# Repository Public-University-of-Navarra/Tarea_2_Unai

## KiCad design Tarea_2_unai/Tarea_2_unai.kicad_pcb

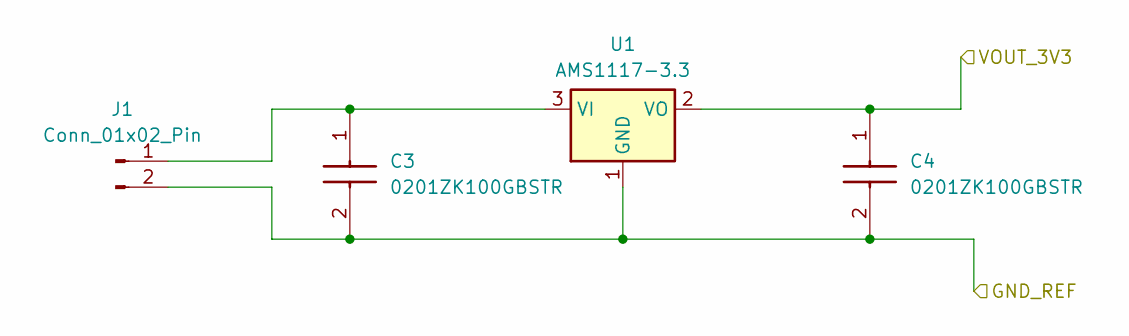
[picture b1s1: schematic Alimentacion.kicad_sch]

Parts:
C3, C4: 0201ZK100GBSTR; CAPC0603X28N; Manufacturer_Part_Number 0201ZK100GBSTR; Mouser Part Number 581-0201ZK100GBSTR
J1: Conn_01x02_Pin; PinHeader_1x04_P2.54mm_Vertical
U1: AMS1117-3.3; SOT-223-3_TabPin2

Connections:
/Alimentacion/GND_REF: C3.2, C4.2, J1.2, U1.1 (GND); also elsewhere on the board
/Alimentacion/VOUT_3V3: C4.1, U1.2 (VO); also elsewhere on the board
unnamed: C3.1, J1.1, U1.3 (VI)

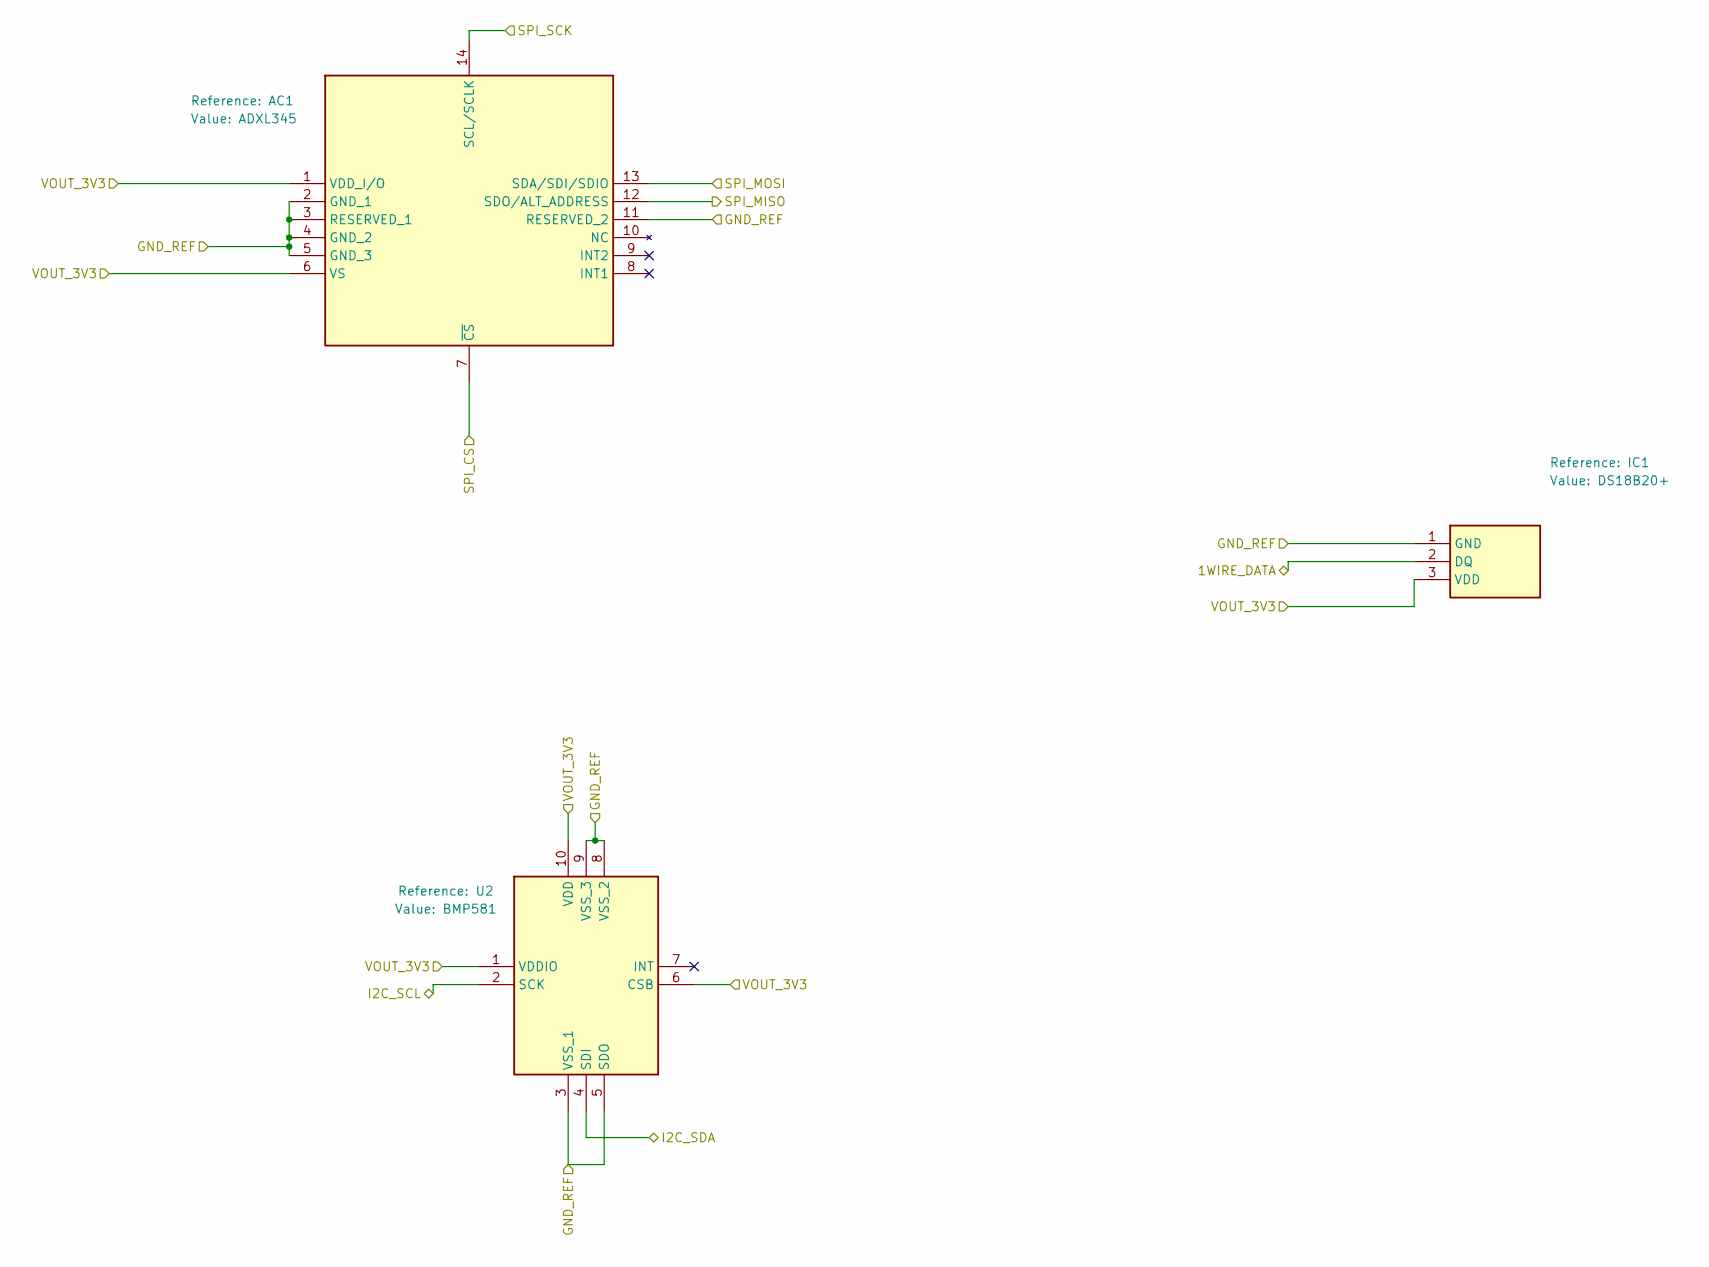
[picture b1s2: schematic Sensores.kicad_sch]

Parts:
AC1: ADXL345; CC-14-1; Manufacturer_Part_Number ADXL345; Mouser Part Number N/A
IC1: DS18B20+; DS18B20; Manufacturer_Part_Number DS18B20+; Mouser Part Number 700-DS18B20+
U2: BMP581; Mouser Part Number 262-BMP581

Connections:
/Alimentacion/GND_REF: AC1.2 (GND_1), AC1.3 (RESERVED_1), AC1.4 (GND_2), AC1.5 (GND_3), AC1.11 (RESERVED_2), IC1.1 (GND), U2.3 (VSS_1), U2.5 (SDO), U2.8 (VSS_2), U2.9 (VSS_3); also elsewhere on the board
/Alimentacion/VOUT_3V3: AC1.1 (VDD_I/O), AC1.6 (VS), IC1.3 (VDD), U2.1 (VDDIO), U2.6 (CSB), U2.10 (VDD); also elsewhere on the board
/Microcontrolador/1WIRE_DATA: IC1.2 (DQ); also elsewhere on the board
/Microcontrolador/I2C_SCL: U2.2 (SCK); also elsewhere on the board
/Microcontrolador/I2C_SDA: U2.4 (SDI); also elsewhere on the board
/Microcontrolador/SPI_CS: AC1.7 (~CS); also elsewhere on the board
/Microcontrolador/SPI_MISO: AC1.12 (SDO/ALT_ADDRESS); also elsewhere on the board
/Microcontrolador/SPI_MOSI: AC1.13 (SDA/SDI/SDIO); also elsewhere on the board
/Microcontrolador/SPI_SCK: AC1.14 (SCL/SCLK); also elsewhere on the board

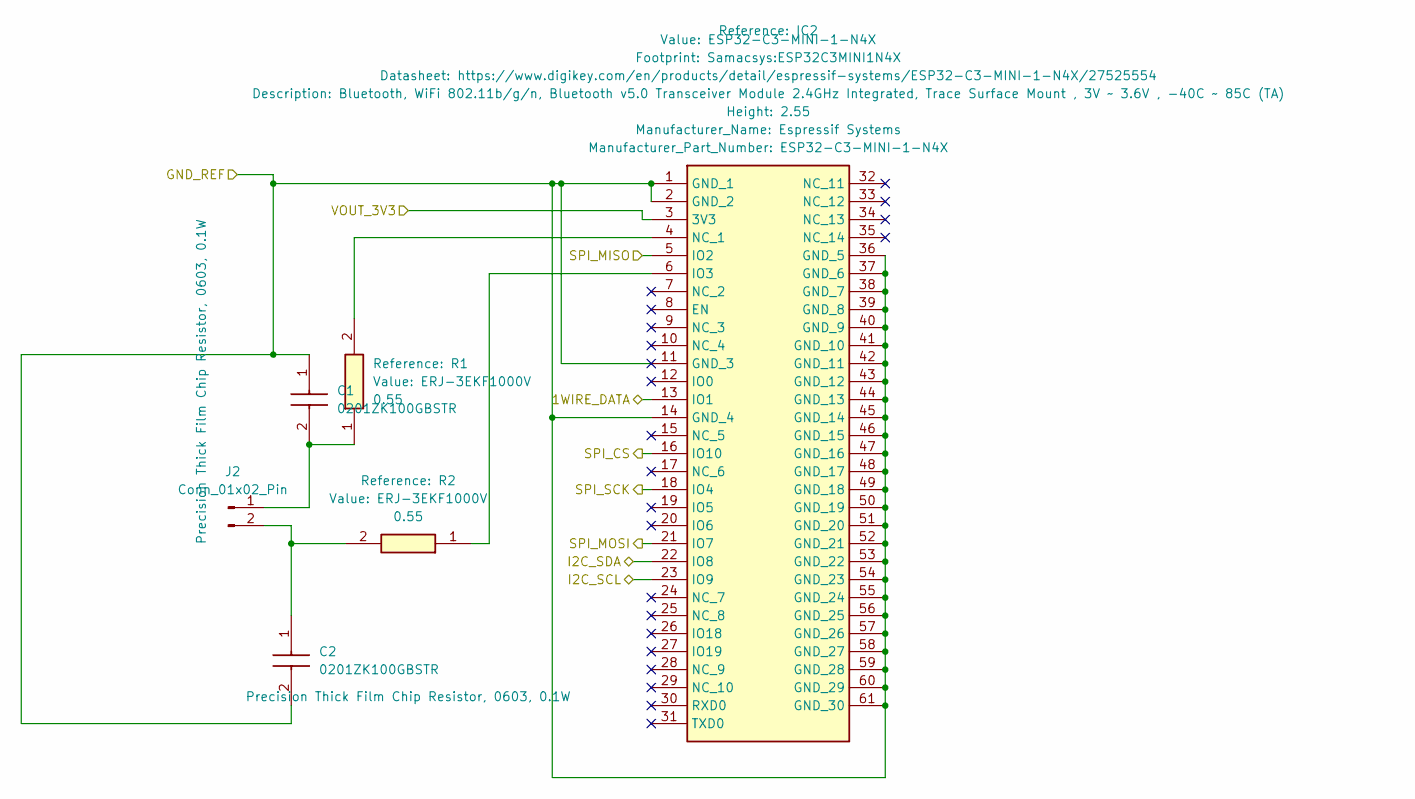
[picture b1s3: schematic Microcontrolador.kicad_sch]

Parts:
C1, C2: 0201ZK100GBSTR; CAPC0603X28N; Manufacturer_Part_Number 0201ZK100GBSTR; Mouser Part Number 581-0201ZK100GBSTR
IC2: ESP32-C3-MINI-1-N4X; ESP32C3MINI1N4X; Manufacturer_Part_Number ESP32-C3-MINI-1-N4X
J2: Conn_01x02_Pin; PinHeader_1x04_P2.54mm_Vertical
R1, R2: ERJ-3EKF1000V; RESC1608X55N; Manufacturer_Part_Number ERJ-3EKF1000V; Mouser Part Number 667-ERJ-3EKF1000V

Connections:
/Alimentacion/GND_REF: C1.1, C2.2, IC2.1 (GND_1), IC2.2 (GND_2), IC2.11 (GND_3), IC2.14 (GND_4), IC2.36 (GND_5), IC2.37 (GND_6), IC2.38 (GND_7), IC2.39 (GND_8), IC2.40 (GND_9), IC2.41 (GND_10), IC2.42 (GND_11), IC2.43 (GND_12), IC2.44 (GND_13), IC2.45 (GND_14), IC2.46 (GND_15), IC2.47 (GND_16), IC2.48 (GND_17), IC2.49 (GND_18), IC2.50 (GND_19), IC2.51 (GND_20), IC2.52 (GND_21), IC2.53 (GND_22), IC2.54 (GND_23), IC2.55 (GND_24), IC2.56 (GND_25), IC2.57 (GND_26), IC2.58 (GND_27), IC2.59 (GND_28), IC2.60 (GND_29), IC2.61 (GND_30); also elsewhere on the board
/Alimentacion/VOUT_3V3: IC2.3 (3V3); also elsewhere on the board
/Microcontrolador/1WIRE_DATA: IC2.13 (IO1); also elsewhere on the board
/Microcontrolador/I2C_SCL: IC2.23 (IO9); also elsewhere on the board
/Microcontrolador/I2C_SDA: IC2.22 (IO8); also elsewhere on the board
/Microcontrolador/SPI_CS: IC2.16 (IO10); also elsewhere on the board
/Microcontrolador/SPI_MISO: IC2.5 (IO2); also elsewhere on the board
/Microcontrolador/SPI_MOSI: IC2.21 (IO7); also elsewhere on the board
/Microcontrolador/SPI_SCK: IC2.18 (IO4); also elsewhere on the board
unnamed: IC2.6 (IO3), R2.1
unnamed: IC2.4 (NC_1), R1.2
unnamed: C1.2, J2.1, R1.1
unnamed: C2.1, J2.2, R2.2

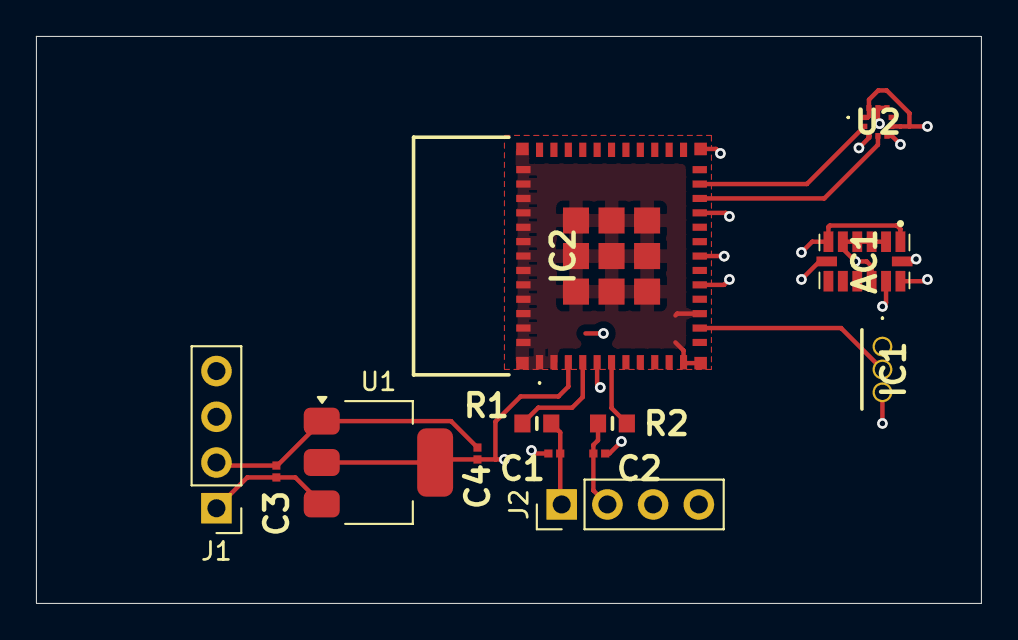
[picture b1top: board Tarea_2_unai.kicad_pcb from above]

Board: 4 copper layers, 52.5 x 31.5 mm, 13 parts (0 on the bottom side), 14 nets.
